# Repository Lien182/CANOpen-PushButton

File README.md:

# CANOpen-PushButton

CANOpen switch button extension for GIRA 2003100 2 3 switch sensor with parallel 24 V interface. The extension supports the usage of the six buttons, the control of the six LEDs + background light and additional temperature measurement.

The firmware of the switch button is based on the CANopenNode project (https://github.com/CANopenNode/CANopenNode).

The CAN network consisting of one or multiple CANOpen-PushButtons can be connected to a TwinCAT-based control system e.g. by using the Beckhoff EL6751 CANOpen Master terminal. TwinCAT supports the scan of CANopen networks. Therefore, the switch buttons don't have to be added manually to the TwinCAT configuration. 

For more help or assembly kits of the hardware please feel free to contact me. Unfortunately, I can not offer complete devices, because legal regulations prevent this.

## TODO
- add more doc

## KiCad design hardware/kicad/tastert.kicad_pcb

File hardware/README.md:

# CAN-Taster_HW

This folder contains the hardware design of the taster created with KiCAD.

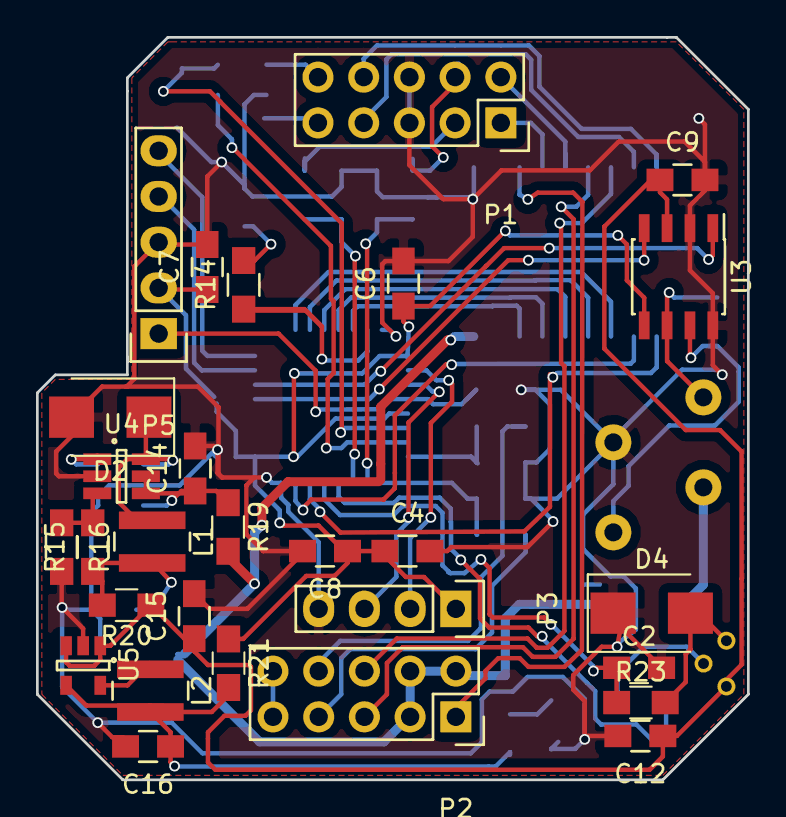
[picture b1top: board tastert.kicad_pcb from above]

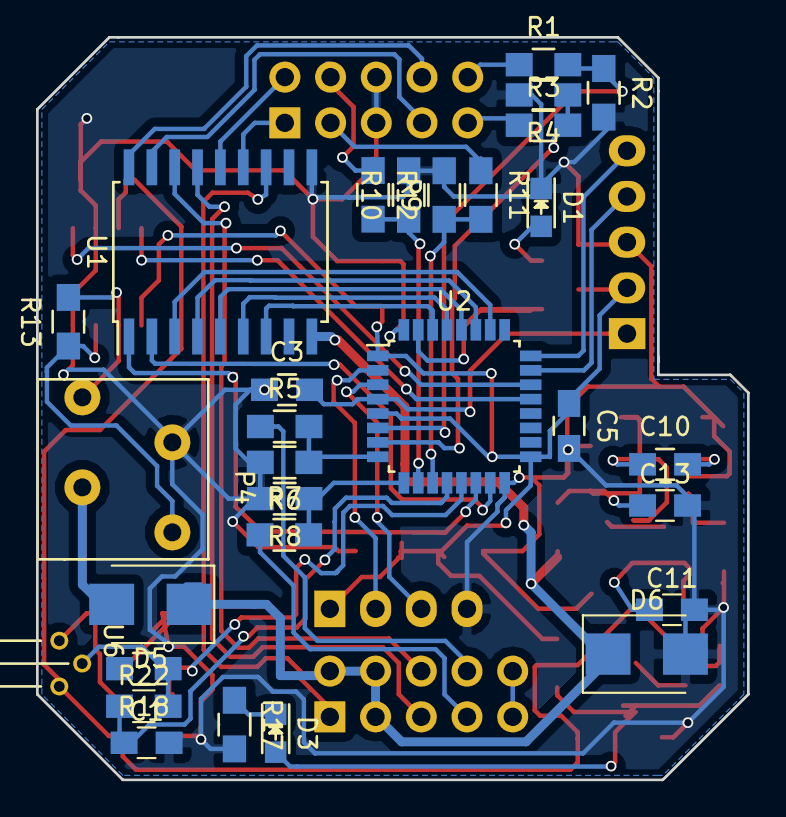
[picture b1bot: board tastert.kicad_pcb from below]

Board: 2 copper layers, 39.5 x 41.2 mm, 58 parts (30 on the bottom side), 55 nets.

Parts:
C1, C2: C; C_0805_HandSoldering
C3, C6, C7, C9, C12, C14: 100n; C_0805_HandSoldering
C4, C10: 1µ; C_0805_HandSoldering
C5: 10n; C_0805_HandSoldering
C8: 4.7µ; C_0805_HandSoldering
C11, C13: 22µ; C_0805_HandSoldering
C15, C16: 10µ; C_0805_HandSoldering
D1: LED; LED_0805
D2, D4, D5, D6: D; D_SMB
D3: LED GN; LED_0805
L1, L2: 10µ; Inductor_Wurth_MAPI-4020
P1, P2: CONN_02X05; Socket_Strip_Straight_2x05
P3: CONN_01X04; Pin_Header_Straight_1x04
P4: CONN_01X04; WAGO_COSTUm
P5: CONN_01X05; Pin_Header_Straight_1x05
R1, R3, R5, R7, R9, R11: 100k; R_0805_HandSoldering
R2, R4, R6, R8, R10, R12: 15k; R_0805_HandSoldering
R13: 120; R_0805_HandSoldering
R14: 390; R_0805_HandSoldering
R15: 8K2; R_0805_HandSoldering
R16: 1K5 1%; R_0805_HandSoldering
R17: 270; R_0805_HandSoldering
R18: 18k; R_0805_HandSoldering
R19, R20, R21: L600R; R_0805_HandSoldering
R22, R23: R; R_0805_HandSoldering
U1: TBD62783AFG; SOIC-18W_7.5x11.6mm_Pitch1.27mm
U2: STM32F042K6Tx; LQFP-32_7x7mm_Pitch0.8mm
U3: MCP2551-I/SN; SOIC-8_3.9x4.9mm_Pitch1.27mm
U4: LM2841; SOT-23-6_Handsoldering
U5: LM3670MF; SOT-23-5
U6: LM35DZ; TO-92_Horizontal1_Molded_Narrow

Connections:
/ADC_TEMP+: C1.1, R22.1, U2.12
/ADC_TEMP-: C2.1, R23.1, U2.13
/CAN_RX: U2.21, U3.4
/CAN_TX: U2.22, U3.1
/I2C_SDA: P3.2, U2.2
/I2C_SDC: P3.3, U2.3
/LED1_24: P1.8, U1.18
/LED1_MC: U1.1, U2.14
/LED2_24: P1.7, U1.17
/LED2_MC: U1.2, U2.15
/LED3_24: P2.6, U1.16
/LED3_MC: U1.3, U2.26
/LED4_24: P2.5, U1.15
/LED4_MC: U1.4, U2.27
/LED5_24: P1.2, U1.14
/LED5_MC: U1.5, U2.28
/LED6_24: P1.1, U1.13
/LED6_MC: U1.6, U2.29
/LEDBL_24: P2.1, U1.12
/LEDBL_MC: U1.7, U2.30
/RUN_LED: R14.1, U2.31
/S1_3.3: R1.2, R2.1, U2.6
/S1_24: P1.10, R1.1
/S2_3.3: R3.2, R4.1, U2.7
/S2_24: P1.9, R3.1
/S3_3.3: R5.2, R6.1, U2.8
/S3_24: P2.8, R5.1
/S4_3.3: R7.2, R8.1, U2.9
/S4_24: P2.7, R7.1
/S5_3.3: R9.2, R10.1, U2.10
/S5_24: P1.4, R9.1
/S6_3.3: R11.2, R12.1, U2.11
/S6_24: P1.3, R11.1
/SYS_NRST: C3.2, P5.1, U2.4
/SYS_SWCLK: P5.5, U2.24
/SYS_SWDIO: P5.4, U2.23
GND: C1.2, C2.2, C3.1, C4.2, C5.2, C6.2, C7.2, C8.2, C9.2, C11.2, C12.2, C13.2, C14.2, C15.2, C16.2, D1.1, D2.2, D4.1, D6.2, P1.5, P1.6, P3.4, P4.4, P5.3, R2.2, R4.2, R6.2, R8.2, R10.2, R12.2, R16.2, R17.2, R18.2, U1.10, U2.16, U2.32, U3.2, U3.8, U4.2, U5.2
unnamed: C10.1, D2.1, L1.1, U4.6
unnamed: C10.2, U4.1
unnamed: C11.1, L1.2, R15.1, R20.2
unnamed: C13.1, C14.1, R19.1, U4.4, U4.5
unnamed: C16.1, D3.2, L2.2, R21.2, U5.4
unnamed: D1.2, R14.2
unnamed: D3.1, R17.1
unnamed: D4.2, R23.2, U6.1
unnamed: D5.2, P4.1
unnamed: L2.1, U5.5
unnamed: P2.9, P2.10
unnamed: P4.2, R13.1, U3.7
unnamed: P4.3, R13.2, U3.6
unnamed: R15.2, R16.1, U4.3
unnamed: R18.1, R22.2, U6.2
VCC3.3: C4.1, C5.1, C6.1, C7.1, C8.1, P3.1, P5.2, R21.1, U2.1, U2.5, U2.17, U3.5
VCC5.0: C9.1, C12.1, C15.1, R20.1, U3.3, U5.1, U5.3, U6.3
VCC24.0: D5.1, D6.1, P2.2, P2.3, P2.4, R19.2, U1.9

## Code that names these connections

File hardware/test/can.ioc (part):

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Mcu.Name=STM32F042K6Tx
Mcu.Package=LQFP32
Mcu.UserName=STM32F042K6Tx
PA0.GPIOParameters=GPIO_Label
PA0.GPIO_Label=Taster_1
PA0.Signal=GPIO_Input
PA1.GPIOParameters=GPIO_Label
PA1.GPIO_Label=Taster_2
PA1.Signal=GPIO_Input
PA11.Mode=Master
PA11.Signal=CAN_RX
PA12.Mode=Master
PA12.Signal=CAN_TX
PA13.Mode=Serial_Wire
PA13.Signal=SYS_SWDIO
PA14.Mode=Serial_Wire
PA14.Signal=SYS_SWCLK
PA2.GPIOParameters=GPIO_Label
PA2.GPIO_Label=Taster_3
PA2.Signal=GPIO_Input
PA3.GPIOParameters=GPIO_Label
PA3.GPIO_Label=Taster_4
PA3.Signal=GPIO_Input
PA4.GPIOParameters=GPIO_Label
PA4.GPIO_Label=Taster_5
PA4.Signal=GPIO_Input
PA5.GPIOParameters=GPIO_Label
PA5.GPIO_Label=Taster_6
PA5.Signal=GPIO_Input
PA6.GPIOParameters=GPIO_Label
PA6.GPIO_Label=ADC_TEMP+
PA6.Mode=IN6
PA6.Signal=ADC_IN6
PA7.GPIOParameters=GPIO_Label
PA7.GPIO_Label=ADC_TEMP-
PA7.Mode=IN7
PA7.Signal=ADC_IN7
PB0.GPIOParameters=GPIO_Label
PB0.GPIO_Label=LED_1
PB0.Signal=GPIO_Output
PB1.GPIOParameters=GPIO_Label
PB1.GPIO_Label=LED_2
PB1.Signal=GPIO_Output
PB3.GPIOParameters=GPIO_Label
PB3.GPIO_Label=LED_3
PB3.Signal=GPIO_Output
PB4.GPIOParameters=GPIO_Label
PB4.GPIO_Label=LED_4
PB4.Signal=GPIO_Output
PB5.GPIOParameters=GPIO_Label
PB5.GPIO_Label=LED_5
PB5.Signal=GPIO_Output
PB6.GPIOParameters=GPIO_Label
PB6.GPIO_Label=LED_6
PB6.Signal=GPIO_Output
PB7.GPIOParameters=GPIO_Label
PB7.GPIO_Label=LED_BL
PB7.Signal=GPIO_Output
PB8.GPIOParameters=GPIO_Label
PB8.GPIO_Label=RUN_LED
PB8.Signal=GPIO_Output
PF0-OSC_IN.Mode=I2C
PF0-OSC_IN.Signal=I2C1_SDA
PF1-OSC_OUT.Mode=I2C
PF1-OSC_OUT.Signal=I2C1_SCL
RCC.SYSCLKFreq_VALUE=48000000
RCC.SYSCLKSource=RCC_SYSCLKSOURCE_PLLCLK
board=can

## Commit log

2021-04-08 Initial check in of sw and hw
2021-04-08 added readme project file
